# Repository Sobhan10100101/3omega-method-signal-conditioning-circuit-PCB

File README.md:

3ω method is the most accurate method to investigate the thermal properties of thin films and bulk materials. Howerver, detection of small voltage variation at the third harmonic needs appropriate signal conditioning circuit to:

1. eliminate the 1st harmonic voltage from the responses which can overload the inputs of the lock-in amplifier
2. Amplify the signals before transferring with long cables to prevent distortion 

A simplified schematic diagram is depicted here:

The detailed description of the circuit and implementation of the experiment is published as **Determination of thermal conductivity, thermal diffusivity and specific heat capacity of porous silicon thin films using the 3ω method** which can be found here: https://authors.elsevier.com/a/1eD-044xa8rMx

Here you can find the image of the final PCB:

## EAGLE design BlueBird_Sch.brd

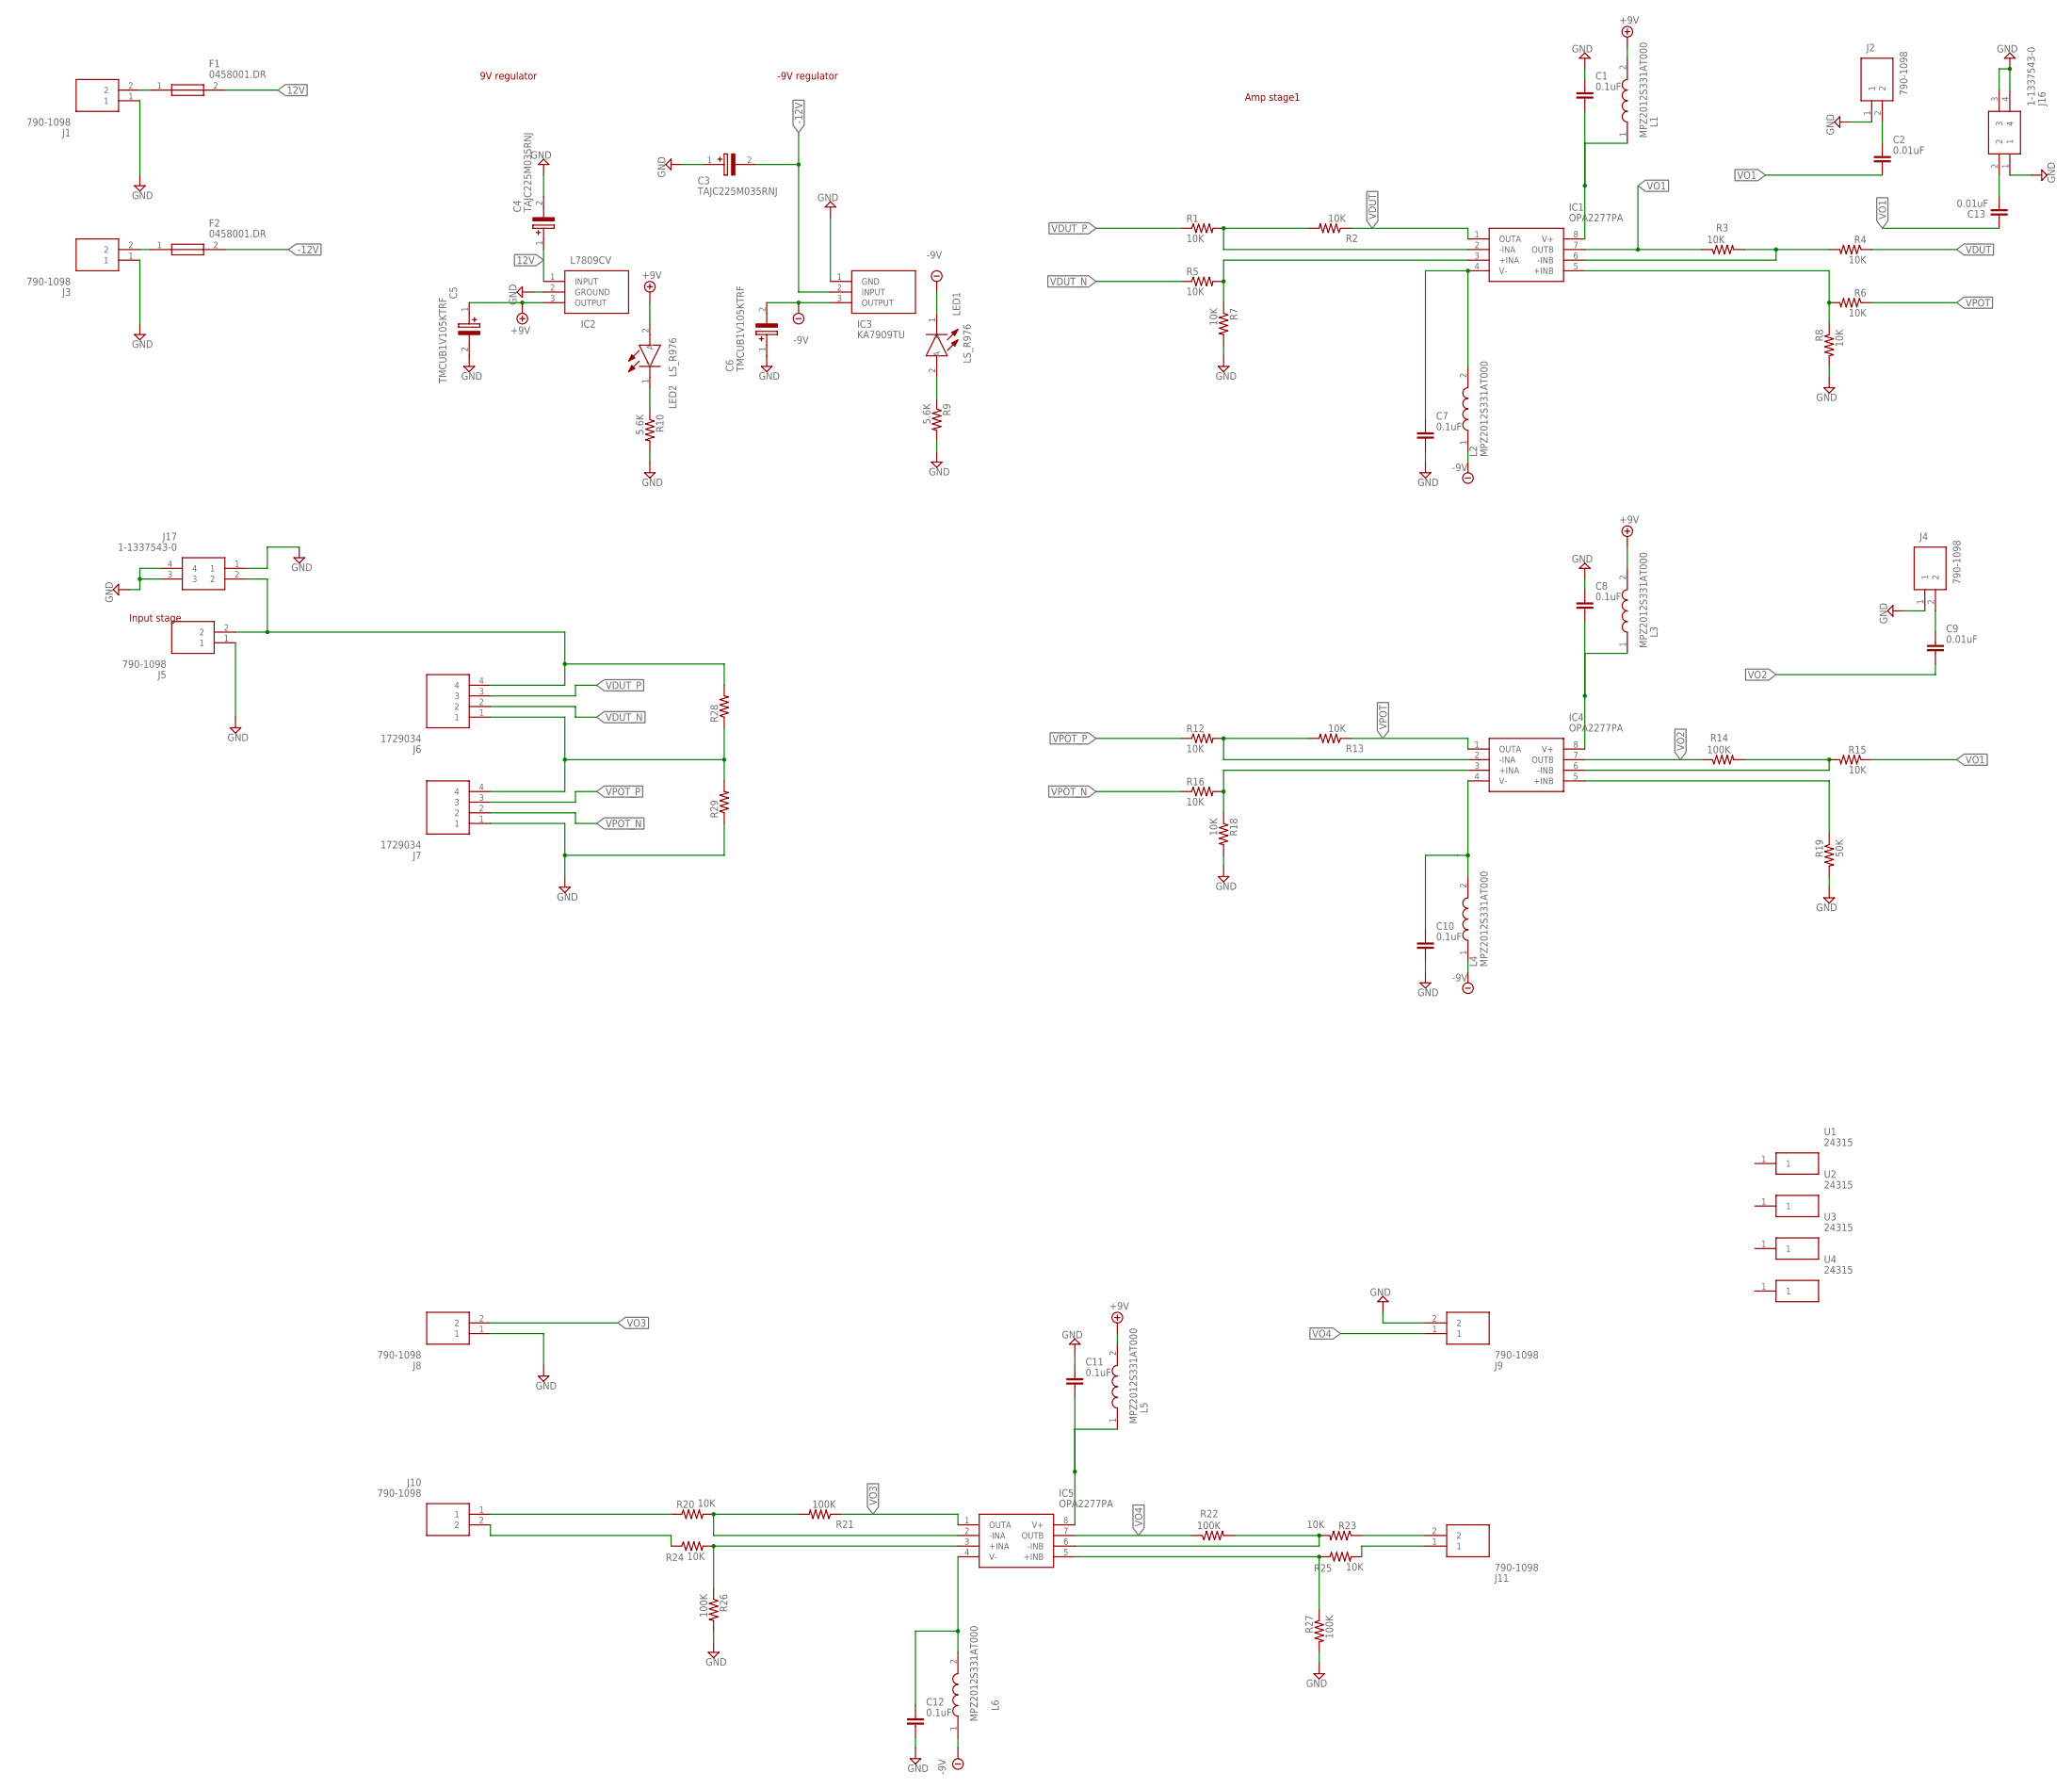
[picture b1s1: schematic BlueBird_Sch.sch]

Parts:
C1, C7, C8, C10, C11, C12: 0.1uF; CAPC2012X110
C2, C9, C13: 0.01uF; CAPC2012X110
C3, C4: TAJC225M035RNJ; CAPPM6032X280N
C5, C6: TMCUB1V105KTRF; CAPPM3528X120N
F1, F2: 0458001.DR; FUSC3215X58N
IC1, IC4, IC5: OPA2277PA; DIP794W53P254L959H508Q8N
IC2: L7809CV; TO255P460X1020X2008-3P
IC3: KA7909TU; TO254P470X1016X2019-3P
J1, J2, J3, J4, J5, J8, J9, J10, J11: 790-1098; 7901098
J6, J7: 1729034; SHDR4W110P0X500_1X4_2000X810X1
J16, J17: 1-1337543-0
L1, L2, L3, L4, L5, L6: MPZ2012S331AT000; INDC2012X105N
LED1, LED2: LS_R976; LEDC2012X40N
R1, R2, R3, R4, R5, R6, R7, R8, R12, R13, R15, R16, R18, R20, R23, R24, R25: 10K; R0805
R9, R10: 5.6K; R0805
R14, R21, R22, R26, R27: 100K; R0805
R19: 50K; R0805
R28, R29: R-US_R1206; R1206
U1, U2, U3, U4: 24315

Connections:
12V: C4.1 (+), F1.2, IC2.1 (INPUT)
+9V: C5.1 (+), IC2.3 (OUTPUT), L1.2, L3.2, L5.2, LED2.2 (A)
-9V: C6.2 (-), IC3.3 (OUTPUT), L2.1, L4.1, L6.1, LED1.1 (K)
-12V: C3.2 (-), F2.2, IC3.2 (INPUT)
GND: C1.1, C3.1 (+), C4.2 (-), C5.2 (-), C6.1 (+), C7.2, C8.1, C10.2, C11.1, C12.2, IC2.2 (GROUND), IC3.1 (GND), J1.1, J2.1, J3.1, J4.1, J5.1, J7.1, J8.1, J9.2, J16.1, J16.3, J16.4, J17.1, J17.3, J17.4, R7.2, R8.2, R9.2, R10.2, R18.2, R19.2, R26.2, R27.2, R29.1
unnamed: F1.1, J1.2
unnamed: F2.1, J3.2
unnamed: C7.1, IC1.4 (V-), L2.2
unnamed: J10.2, R24.1
unnamed: J10.1, R20.1
unnamed: J5.2, J6.4, J17.2, R28.2
unnamed: J11.2, R23.1
unnamed: J11.1, R25.2
unnamed: C9.1, J4.2
unnamed: C2.1, J2.2
unnamed: LED1.2 (A), R9.1
unnamed: LED2.1 (K), R10.1
unnamed: C13.1, J16.2
unnamed: J6.1, J7.4, R28.1, R29.2
unnamed: IC1.2 (-INA), R1.2, R2.2
unnamed: IC1.3 (+INA), R5.2, R7.1
unnamed: C8.2, IC4.8 (V+), L3.1
unnamed: C1.2, IC1.8 (V+), L1.1
unnamed: C11.2, IC5.8 (V+), L5.1
unnamed: IC1.6 (-INB), R3.2, R4.2
unnamed: IC1.5 (+INB), R6.2, R8.1
unnamed: C10.1, IC4.4 (V-), L4.2
unnamed: IC4.2 (-INA), R12.2, R13.2
unnamed: IC4.3 (+INA), R16.2, R18.1
unnamed: C12.1, IC5.4 (V-), L6.2
unnamed: IC4.6 (-INB), R14.2, R15.2
unnamed: IC4.5 (+INB), R19.1
unnamed: IC5.2 (-INA), R20.2, R21.2
unnamed: IC5.3 (+INA), R24.2, R26.1
unnamed: IC5.6 (-INB), R22.2, R23.2
unnamed: IC5.5 (+INB), R25.1, R27.1
VDUT: IC1.1 (OUTA), R2.1, R4.1
VDUT_N: J6.2, R5.1
VDUT_P: J6.3, R1.1
VO1: C2.2, C13.2, IC1.7 (OUTB), R3.1, R15.1
VO2: C9.2, IC4.7 (OUTB), R14.1
VO3: IC5.1 (OUTA), J8.2, R21.1
VO4: IC5.7 (OUTB), J9.1, R22.1
VPOT: IC4.1 (OUTA), R6.1, R13.1
VPOT_N: J7.2, R16.1
VPOT_P: J7.3, R12.1

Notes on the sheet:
9V regulator
-9V regulator
Amp stage1
Input stage

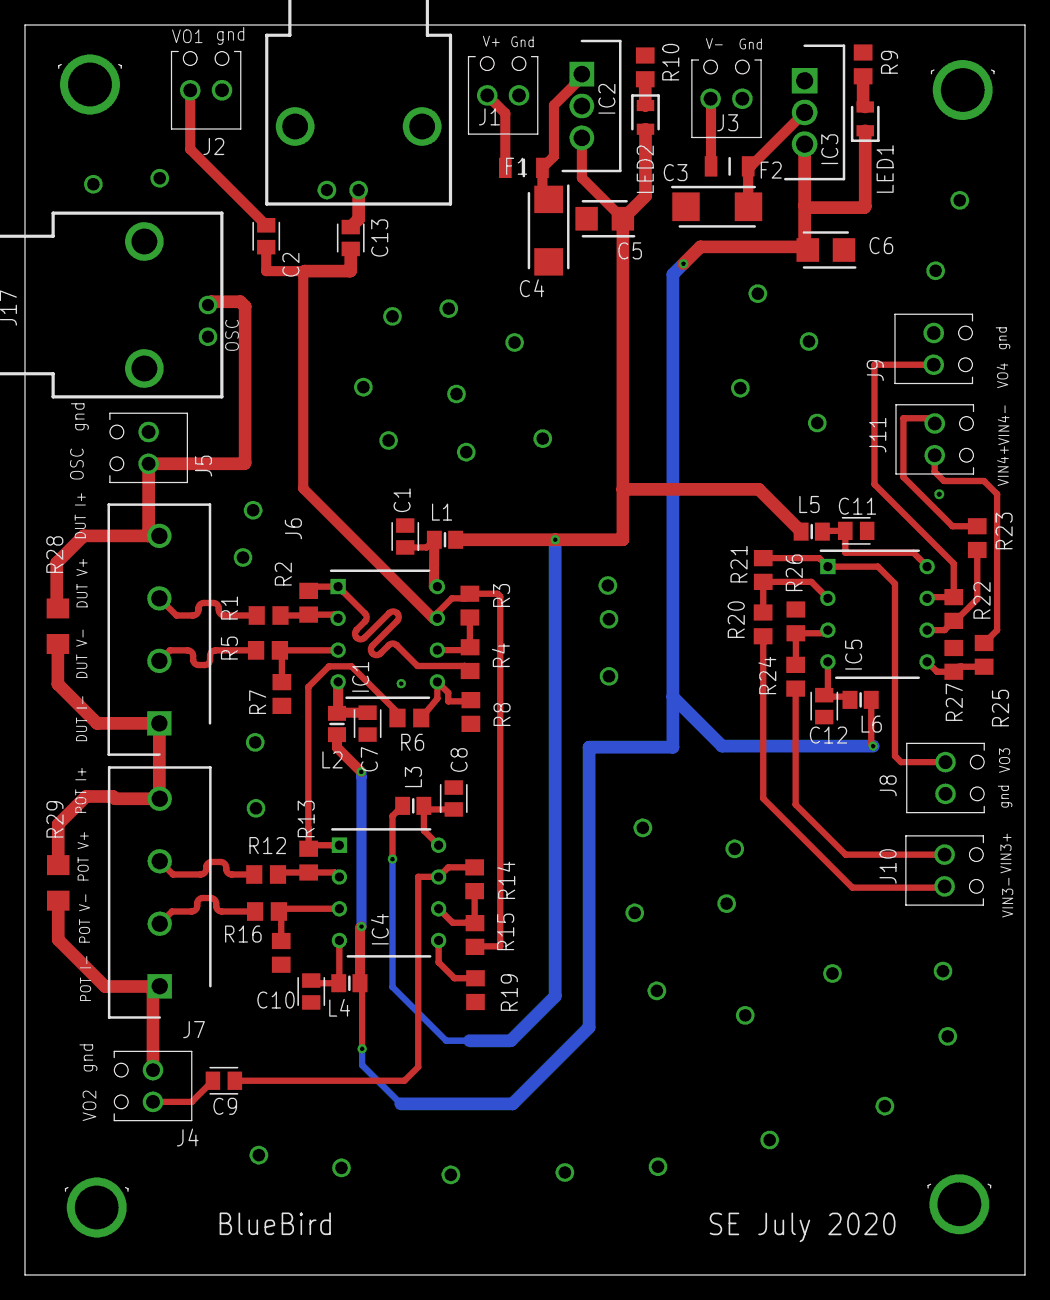
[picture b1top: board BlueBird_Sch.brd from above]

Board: 2 copper layers, 80.0 x 100.0 mm, 72 parts (0 on the bottom side), 46 nets.

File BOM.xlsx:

Partlist exported from C:/OneDrive - The University of Western Australia/PhD/13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
Part Value Device Package Description ALLIED_NUMBER CATEGORY DESCRIPTION HEIGHT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
C1 0.1uF C_CHIP-0805(2012-METRIC) CAPC2012X110 Capacitor - Generic Capacitor
C2 0.01uF C_CHIP-0805(2012-METRIC) CAPC2012X110 Capacitor - Generic Capacitor
C3 TAJC225M035RNJ TAJC225M035RNJ CAPPM6032X280N Tantalum Capacitors - Solid SMD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
C4 TAJC225M035RNJ TAJC225M035RNJ CAPPM6032X280N Tantalum Capacitors - Solid SMD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
C5 TMCUB1V105KTRF TMCUB1V105KTRF CAPPM3528X120N Cap Tant Solid 1uF 35V UB CASE 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
C6 TMCUB1V105KTRF TMCUB1V105KTRF CAPPM3528X120N Cap Tant Solid 1uF 35V UB CASE 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
C7 0.1uF C_CHIP-0805(2012-METRIC) CAPC2012X110 Capacitor - Generic Capacitor
C8 0.1uF C_CHIP-0805(2012-METRIC) CAPC2012X110 Capacitor - Generic Capacitor
C9 0.01uF C_CHIP-0805(2012-METRIC) CAPC2012X110 Capacitor - Generic Capacitor
C10 0.1uF C_CHIP-0805(2012-METRIC) CAPC2012X110 Capacitor - Generic Capacitor
C11 0.1uF C_CHIP-0805(2012-METRIC) CAPC2012X110 Capacitor - Generic Capacitor
C12 0.1uF C_CHIP-0805(2012-METRIC) CAPC2012X110 Capacitor - Generic Capacitor
F1 0458001.DR 0458001.DR FUSC3215X58N LITTELFUSE - 0458001.DR - Fuse, Surface M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
F2 0458001.DR 0458001.DR FUSC3215X58N LITTELFUSE - 0458001.DR - Fuse, Surface M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
IC1 OPA2277PA OPA2277PA DIP794W53P254L959H508Q8N Dual precision op-amp,OPA2277P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
IC2 L7809CV L7809CV TO255P460X1020X2008-3P Standard Regulator 9V 1.5A STMicroel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
IC3 KA7909TU KA7909TU TO254P470X1016X2019-3P ON Semiconductor, -9 V Linear Volt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
IC4 OPA2277PA OPA2277PA DIP794W53P254L959H508Q8N Dual precision op-amp,OPA2277P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
IC5 OPA2277PA OPA2277PA DIP794W53P254L959H508Q8N Dual precision op-amp,OPA2277P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
J1 790-1098 790-1098 7901098 2 Way PCB Terminal Strip 2 Way PCB Terminal Strip 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
J2 790-1098 790-1098 7901098 2 Way PCB Terminal Strip 2 Way PCB Terminal Strip 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
J3 790-1098 790-1098 7901098 2 Way PCB Terminal Strip 2 Way PCB Terminal Strip 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
J4 790-1098 790-1098 7901098 2 Way PCB Terminal Strip 2 Way PCB Terminal Strip 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
J5 790-1098 790-1098 7901098 2 Way PCB Terminal Strip 2 Way PCB Terminal Strip 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
J6 1729034 1729034 SHDR4W110P0X500_1X4_2000X810X1 Low profile PCB terminal bloc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
J7 1729034 1729034 SHDR4W110P0X500_1X4_2000X810X1 Low profile PCB terminal bloc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
J8 790-1098 790-1098 7901098 2 Way PCB Terminal Strip 2 Way PCB Terminal Strip 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
J9 790-1098 790-1098 7901098 2 Way PCB Terminal Strip 2 Way PCB Terminal Strip 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
J10 790-1098 790-1098 7901098 2 Way PCB Terminal Strip 2 Way PCB Terminal Strip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
J11 790-1098 790-1098 7901098 2 Way PCB Terminal Strip 2 Way PCB Terminal Strip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
J12 R25-3001602 R25-3001602 R253001602 Standoffs & Spacers M2.5 x 16mm HEX M/F 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
J13 R25-3001602 R25-3001602 R253001602 Standoffs & Spacers M2.5 x 16mm HEX M/F 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
J14 R25-3001602 R25-3001602 R253001602 Standoffs & Spacers M2.5 x 16mm HEX M/F 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
L1 MPZ2012S331AT000 MPZ2012S331AT000 INDC2012X105N Ferrite Beads Multi-Layer Po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
L2 MPZ2012S331AT000 MPZ2012S331AT000 INDC2012X105N Ferrite Beads Multi-Layer Po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
L3 MPZ2012S331AT000 MPZ2012S331AT000 INDC2012X105N Ferrite Beads Multi-Layer Po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
L4 MPZ2012S331AT000 MPZ2012S331AT000 INDC2012X105N Ferrite Beads Multi-Layer Po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
L5 MPZ2012S331AT000 MPZ2012S331AT000 INDC2012X105N Ferrite Beads Multi-Layer Po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
L6 MPZ2012S331AT000 MPZ2012S331AT000 INDC2012X105N Ferrite Beads Multi-Layer Po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
LED1 LS_R976 LS_R976 LEDC2012X40N Red 0805 CHIPLED LS R976N-R102 Osram Opto LS 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
LED2 LS_R976 LS_R976 LEDC2012X40N Red 0805 CHIPLED LS R976N-R102 Osram Opto LS 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
R1 10K R-US_R0402 R0402 RESISTOR, American symbol
R2 10K R-US_R0402 R0402 RESISTOR, American symbol
R3 10K R-US_R0402 R0402 RESISTOR, American symbol
R4 10K R-US_R0402 R0402 RESISTOR, American symbol
R5 10K R-US_R0402 R0402 RESISTOR, American symbol
R6 10K R-US_R0402 R0402 RESISTOR, American symbol
R7 10K R-US_R0402 R0402 RESISTOR, American symbol
R8 10K R-US_R0402 R0402 RESISTOR, American symbol
R9 5.6K R-US_R0402 R0402 RESISTOR, American symbol
R10 5.6K R-US_R0402 R0402 RESISTOR, American symbol
R11 200 R-US_R0402 R0402 RESISTOR, American symbol
R12 10K R-US_R0402 R0402 RESISTOR, American symbol
R13 10K R-US_R0402 R0402 RESISTOR, American symbol
R14 10K R-US_R0402 R0402 RESISTOR, American symbol
R15 10K R-US_R0402 R0402 RESISTOR, American symbol
R16 10K R-US_R0402 R0402 RESISTOR, American symbol
R17 100 R-US_R0402 R0402 RESISTOR, American symbol
R18 10K R-US_R0402 R0402 RESISTOR, American symbol
R19 50K R-US_R0402 R0402 RESISTOR, American symbol
R20 10K R-US_R0402 R0402 RESISTOR, American symbol
R21 100K R-US_R0402 R0402 RESISTOR, American symbol
R22 100K R-US_R0402 R0402 RESISTOR, American symbol
R23 10K R-US_R0402 R0402 RESISTOR, American symbol
R24 10K R-US_R0402 R0402 RESISTOR, American symbol
R25 10K R-US_R0402 R0402 RESISTOR, American symbol
R26 100K R-US_R0402 R0402 RESISTOR, American symbol
R27 100K R-US_R0402 R0402 RESISTOR, American symbol
